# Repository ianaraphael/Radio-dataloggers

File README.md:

# SNICE_therm
Snow/ice thermistor dataloggers

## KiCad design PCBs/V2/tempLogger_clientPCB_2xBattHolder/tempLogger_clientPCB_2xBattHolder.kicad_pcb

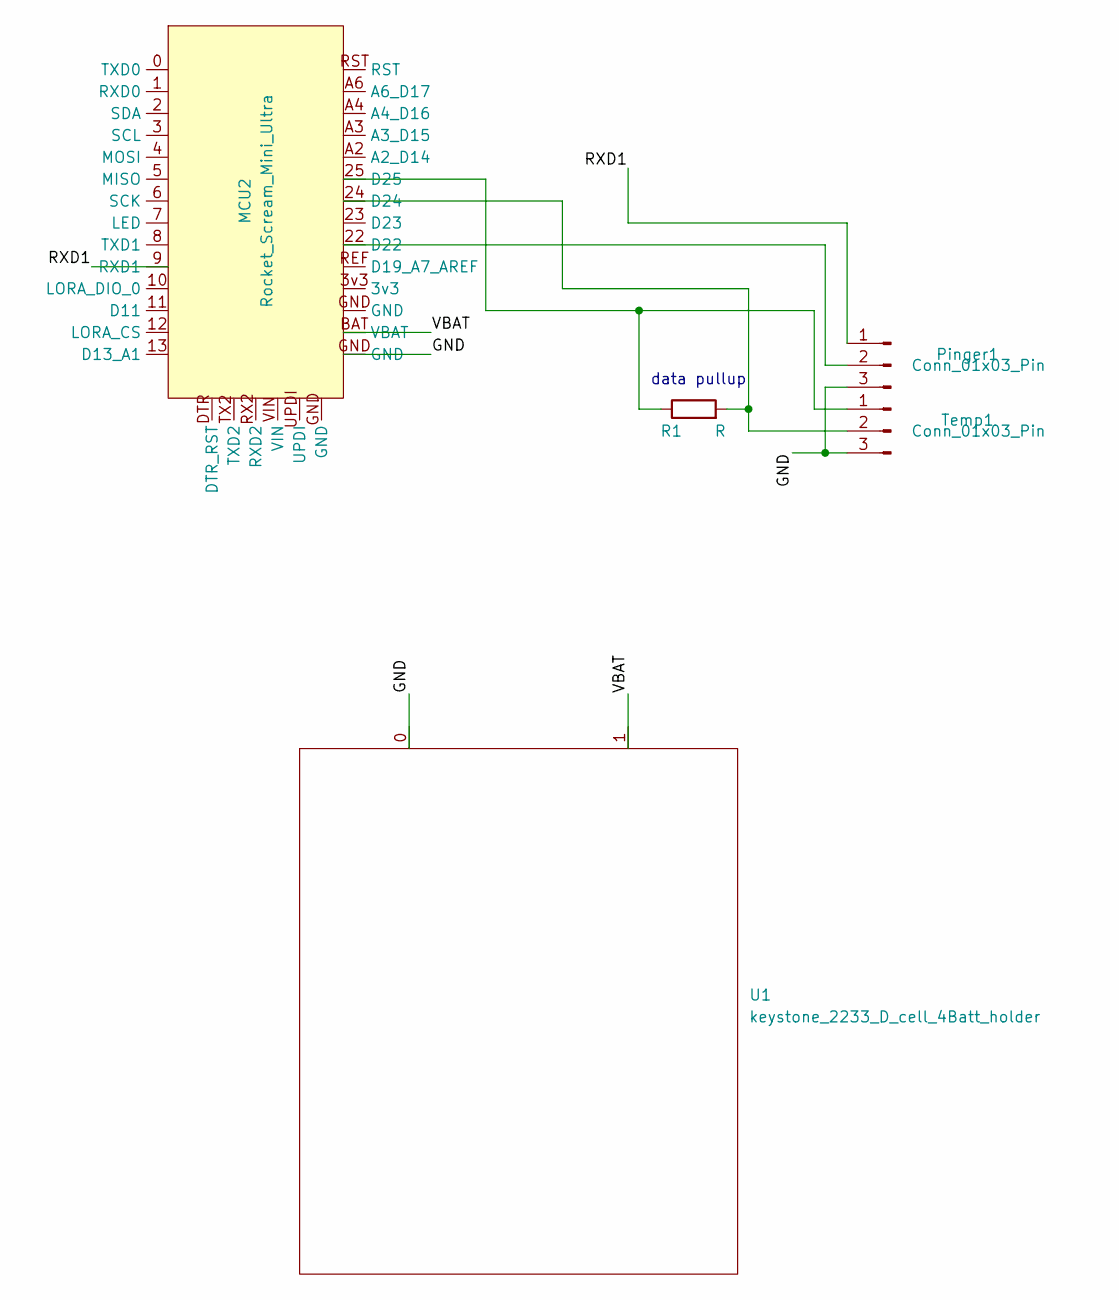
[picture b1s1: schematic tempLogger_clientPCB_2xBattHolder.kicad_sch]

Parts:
MCU2: Rocket_Scream_Mini_Ultra
Pinger1: Conn_01x03_Pin; Molex_KK-254_AE-6410-03A_1x03_P2.54mm_Vertical
R1: R; R_Axial_DIN0204_L3.6mm_D1.6mm_P7.62mm_Horizontal
Temp1: Conn_01x03_Pin; Molex_KK-254_AE-6410-03A_1x03_P2.54mm_Vertical
U1: keystone_2233_D_cell_4Batt_holder; BatteryHolder_Keystone_2233_4Cell

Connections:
/GND: MCU2.GND, Pinger1.3, Temp1.3, U1.0
/RXD1: MCU2.9 (RXD1), Pinger1.1
/VBAT: MCU2.BAT (VBAT), U1.1
unnamed: MCU2.22 (D22), Pinger1.2
unnamed: MCU2.24 (D24), R1.2, Temp1.2
unnamed: MCU2.25 (D25), R1.1, Temp1.1

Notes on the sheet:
data pullup

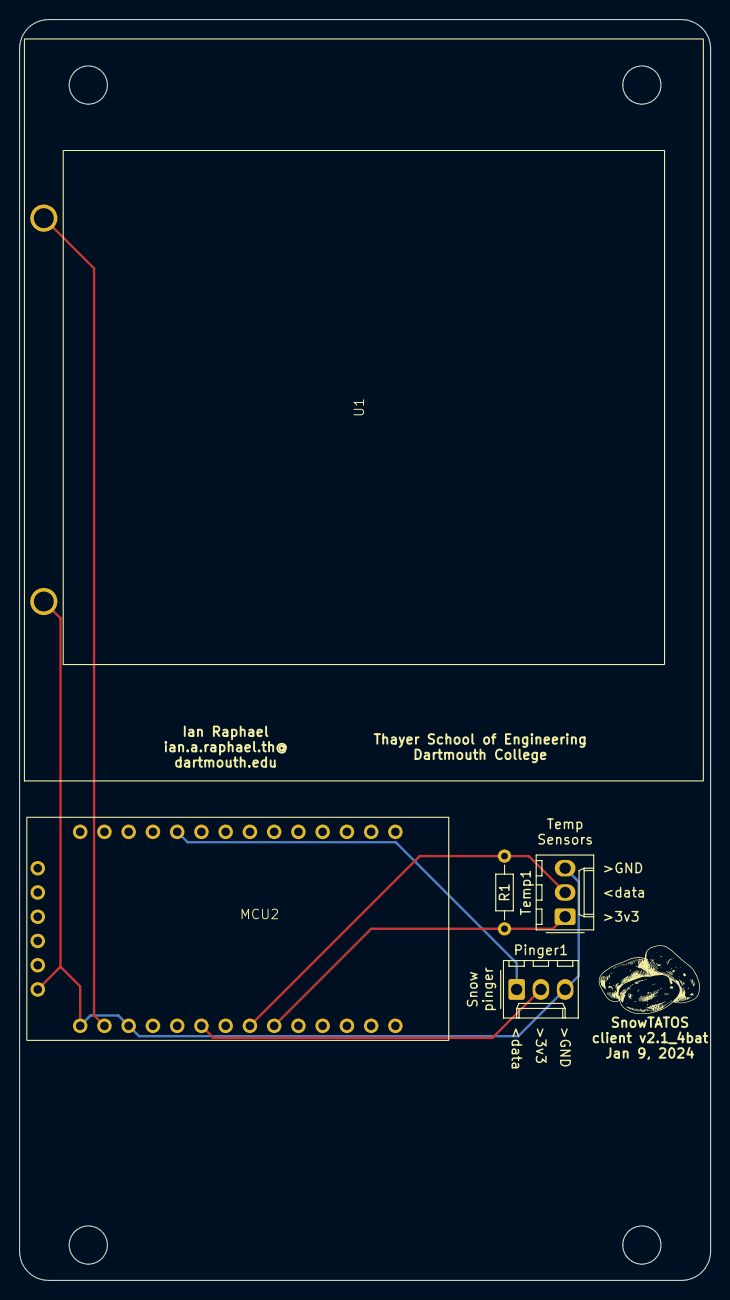
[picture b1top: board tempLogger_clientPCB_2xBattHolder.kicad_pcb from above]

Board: 2 copper layers, 72.4 x 132.1 mm, 5 parts (0 on the bottom side), 6 nets.

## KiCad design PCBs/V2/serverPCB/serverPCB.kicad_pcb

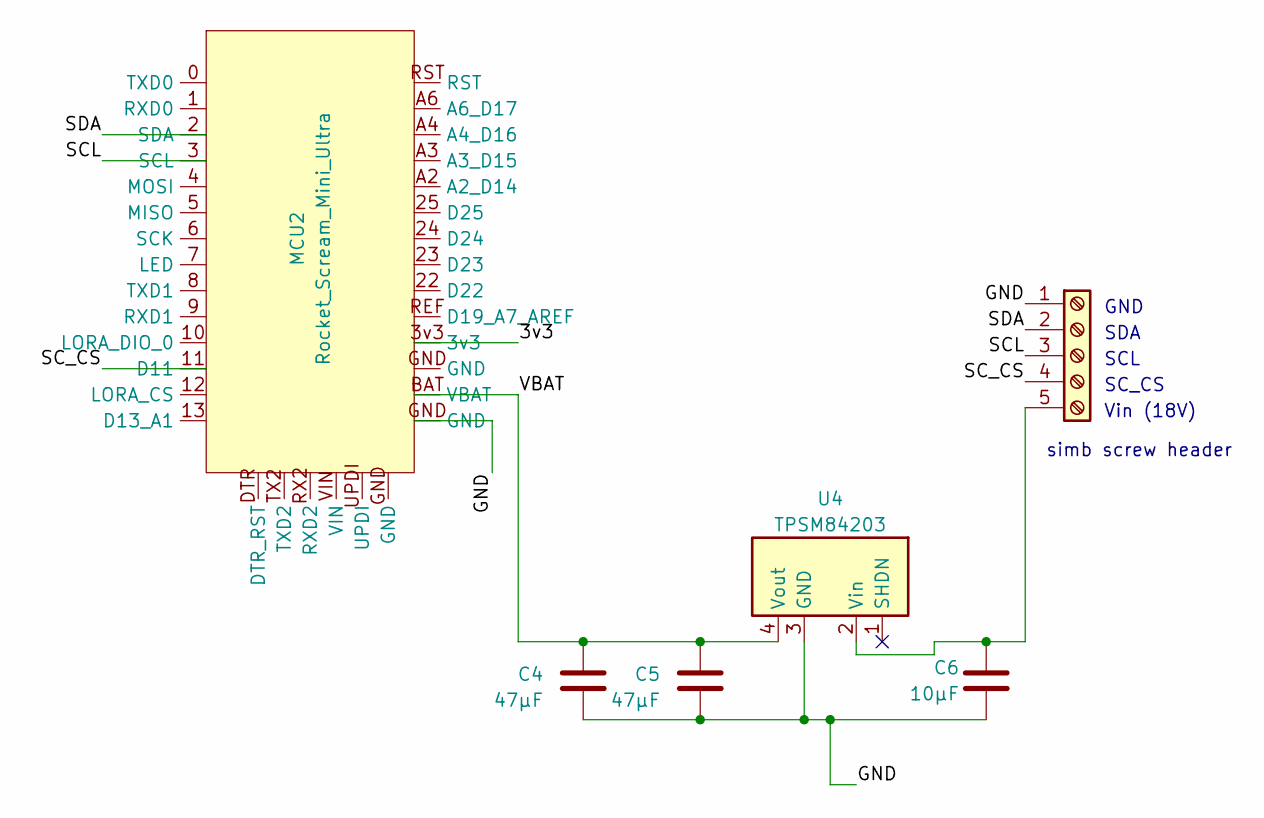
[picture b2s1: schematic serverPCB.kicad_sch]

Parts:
C4, C5: 47µF; CP_Radial_Tantal_D4.5mm_P2.50mm
C6: 10µF; CP_Radial_Tantal_D4.5mm_P2.50mm
J2: Screw_Terminal_01x04; TerminalBlock_Phoenix_MPT-0,5-5-2.54_1x05_P2.54mm_Horizontal
MCU2: Rocket_Scream_Mini_Ultra
U4: TPSM84203; Pololu_D24V5F9

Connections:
/3v3: MCU2.3v3
/GND: C4.2, C5.2, C6.2, J2.1, MCU2.GND, U4.3 (GND)
/SCL: J2.3, MCU2.3 (SCL)
/SC_CS: J2.4, MCU2.11 (D11)
/SDA: J2.2, MCU2.2 (SDA)
/VBAT: C4.1, C5.1, MCU2.BAT (VBAT), U4.4 (Vout)
unnamed: C6.1, J2.5, U4.2 (Vin)

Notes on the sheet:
simb screw header
SCL
SC_CS
SDA
Vin (18V)
GND

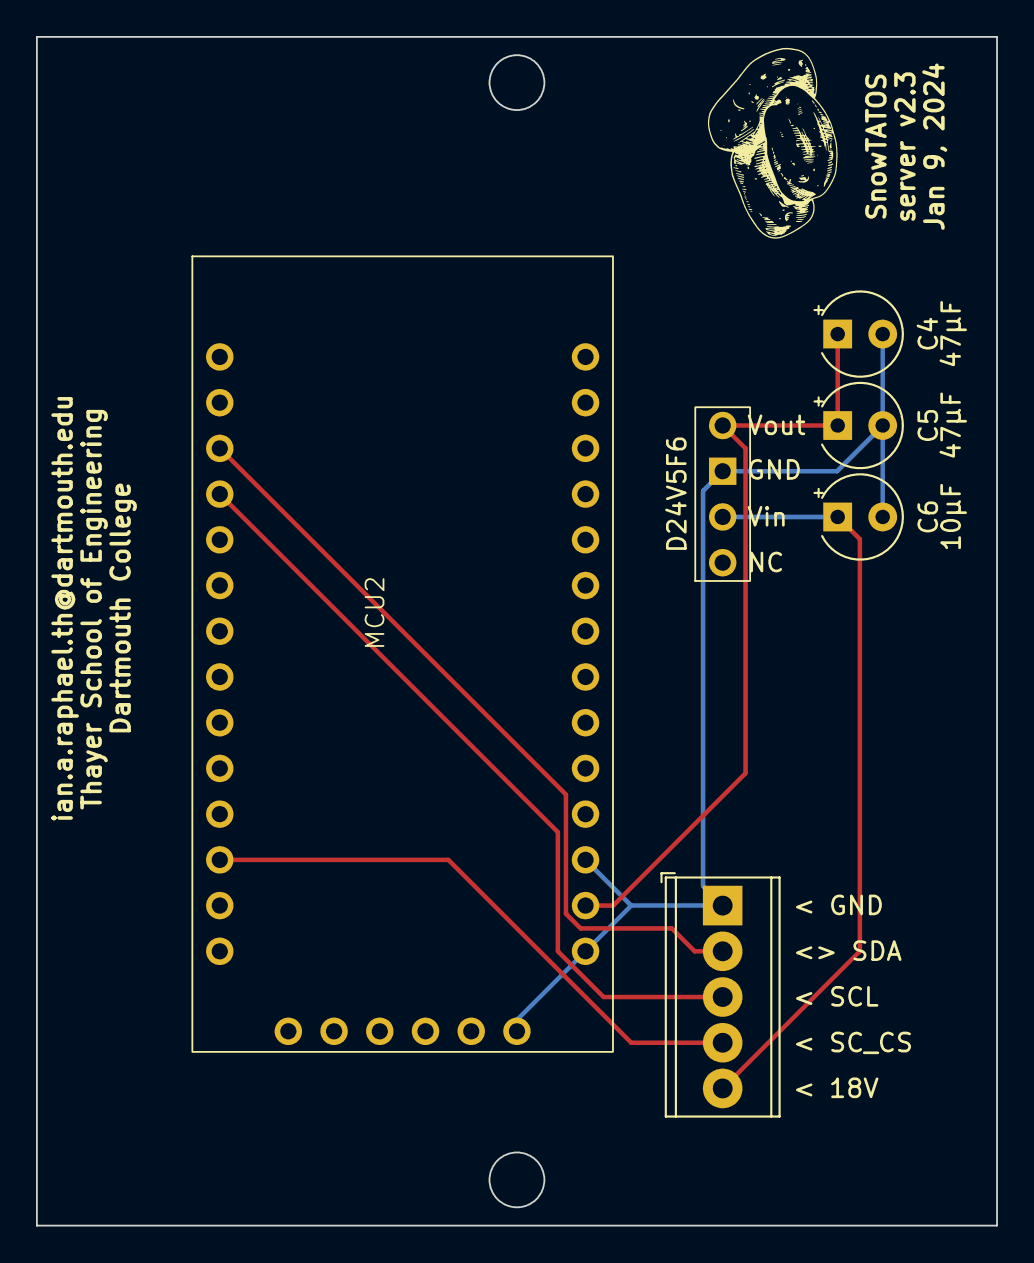
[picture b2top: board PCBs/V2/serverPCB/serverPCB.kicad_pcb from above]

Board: 2 copper layers, 53.3 x 66.0 mm, 6 parts (0 on the bottom side), 6 nets.

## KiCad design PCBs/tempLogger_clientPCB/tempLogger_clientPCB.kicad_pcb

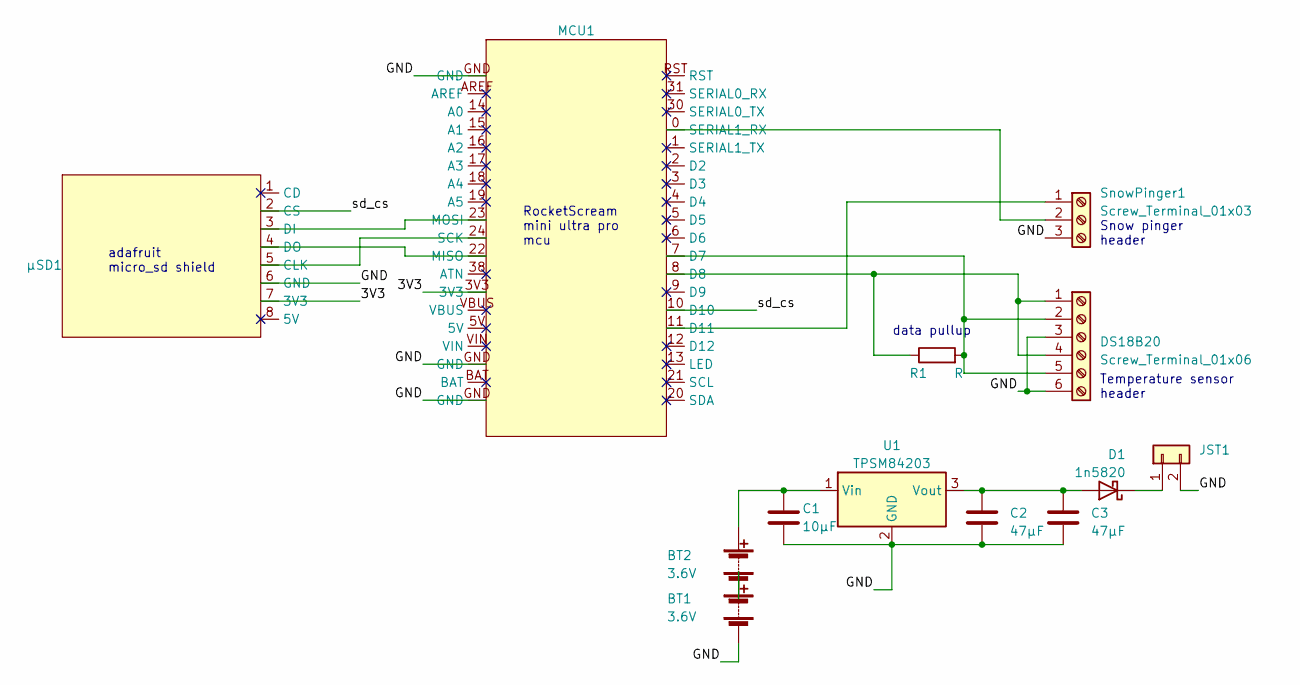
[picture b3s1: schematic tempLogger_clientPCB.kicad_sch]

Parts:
BT1, BT2: 3.6V; battery_c_cell_solderTabs
C1: 10µF; CP_Radial_Tantal_D4.5mm_P2.50mm
C2, C3: 47µF; CP_Radial_Tantal_D4.5mm_P2.50mm
D1: 1n5820; D_DO-41_SOD81_P10.16mm_Horizontal
DS18B20: Screw_Terminal_01x06; TerminalBlock_Phoenix_MPT-0,5-6-2.54_1x06_P2.54mm_Horizontal
JST1: JST male flying leads; TestPoint_2Pads_Pitch5.08mm_Drill1.3mm
MCU1: Rocket_Scream_Mini_Ultra_Pro
R1: R; R_Axial_DIN0204_L3.6mm_D1.6mm_P7.62mm_Horizontal
SnowPinger1: Screw_Terminal_01x03; TerminalBlock_TE_282834-3_1x03_P2.54mm_Horizontal
U1: TPSM84203; Converter_DCDC_TRACO_TSR-1_THT
µSD1: micro_sd_cardReader_adafruit

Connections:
/3V3: MCU1.3V3, µSD1.7 (3V3)
/GND: BT1.2 (-), C1.2, C2.2, C3.2, DS18B20.3, DS18B20.6, JST1.2, MCU1.GND, SnowPinger1.3, U1.2 (GND), µSD1.6 (GND); also elsewhere on the board
/sd_cs: MCU1.10 (D10), µSD1.2 (CS)
unnamed: BT1.1 (+), BT2.2 (-)
unnamed: BT2.1 (+), C1.1, U1.1 (Vin)
unnamed: C2.1, C3.1, D1.2 (A), U1.3 (Vout)
unnamed: D1.1 (K), JST1.1
unnamed: DS18B20.1, DS18B20.4, MCU1.8 (D8), R1.1
unnamed: DS18B20.2, DS18B20.5, MCU1.7 (D7), R1.2
unnamed 9: MCU1.11 (D11), SnowPinger1.1; also elsewhere on the board
unnamed: MCU1.22 (MISO), µSD1.4 (DO)
unnamed: MCU1.23 (MOSI), µSD1.3 (DI)
unnamed: MCU1.24 (SCK), µSD1.5 (CLK)
unnamed 13: MCU1.0 (SERIAL1_RX), SnowPinger1.2; also elsewhere on the board

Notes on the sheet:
RocketScream mini ultra pro mcu
data pullup
adafruit micro_sd shield
Temperature sensor header
Snow pinger header

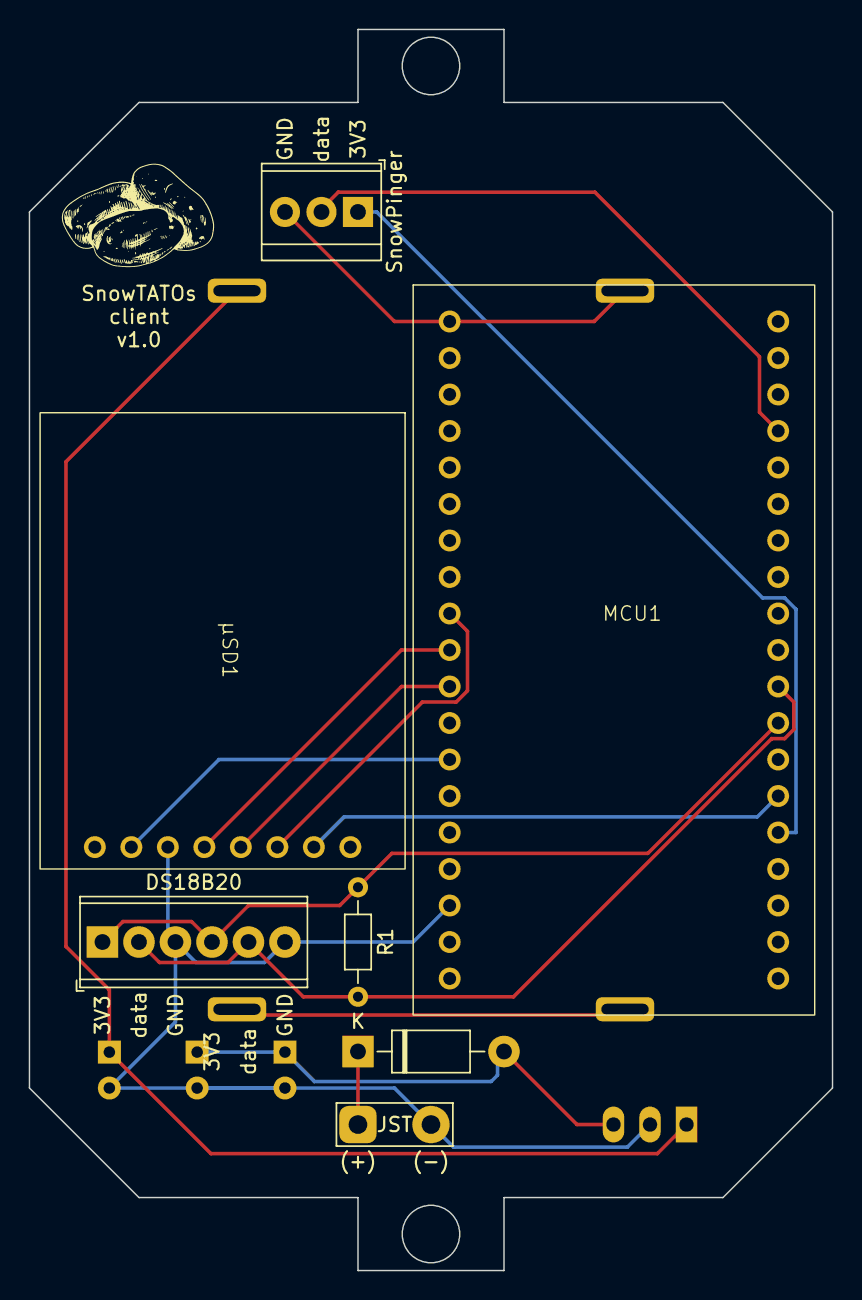
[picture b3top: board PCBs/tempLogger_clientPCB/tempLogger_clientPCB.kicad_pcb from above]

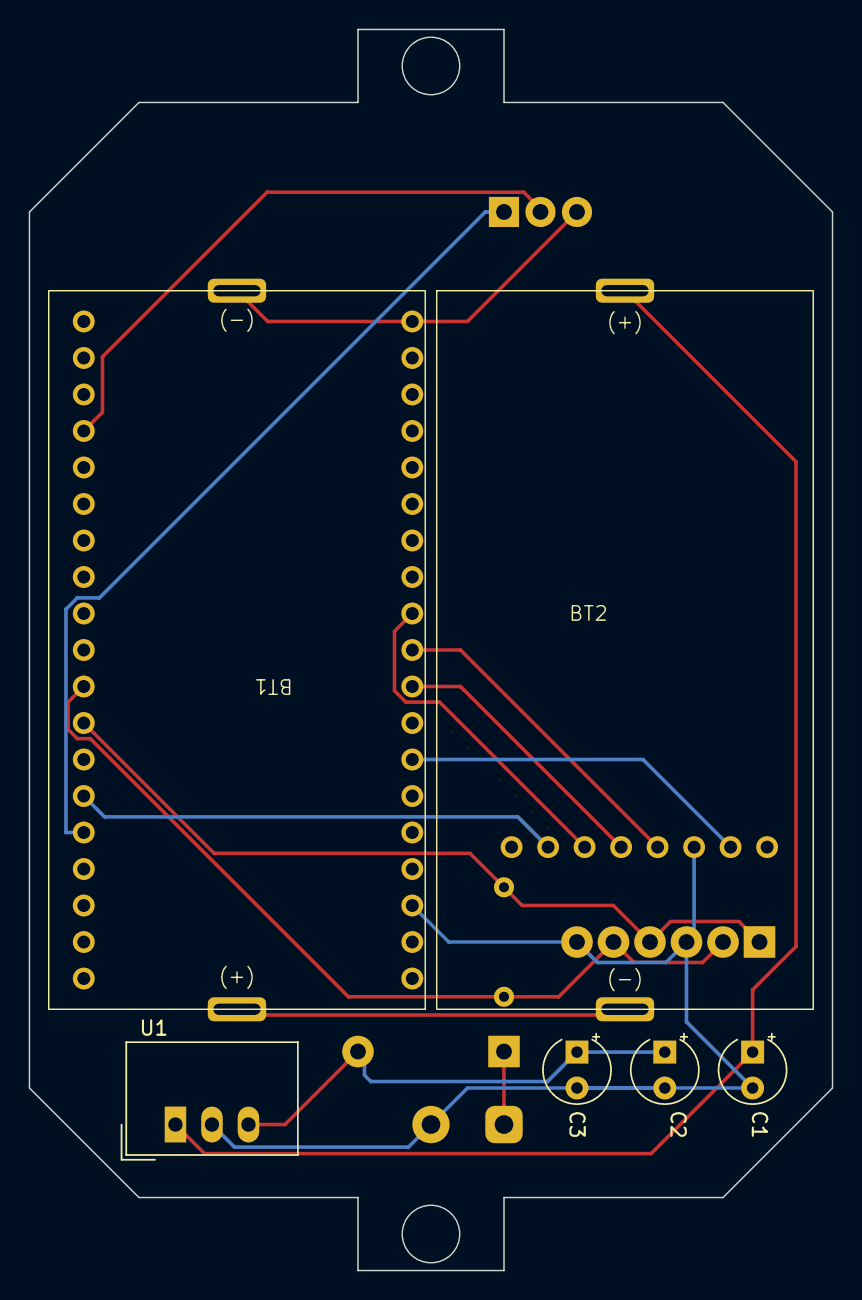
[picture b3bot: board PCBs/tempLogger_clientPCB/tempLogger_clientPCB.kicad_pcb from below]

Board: 2 copper layers, 55.9 x 86.4 mm, 13 parts (6 on the bottom side), 14 nets.

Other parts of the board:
SnowPinger: Screw_Terminal_01x03; TerminalBlock_TE_282834-3_1x03_P2.54mm_Horizontal

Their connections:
/GND: SnowPinger.3; also elsewhere on the board
unnamed 9: SnowPinger.1; also elsewhere on the board
unnamed 13: SnowPinger.2; also elsewhere on the board

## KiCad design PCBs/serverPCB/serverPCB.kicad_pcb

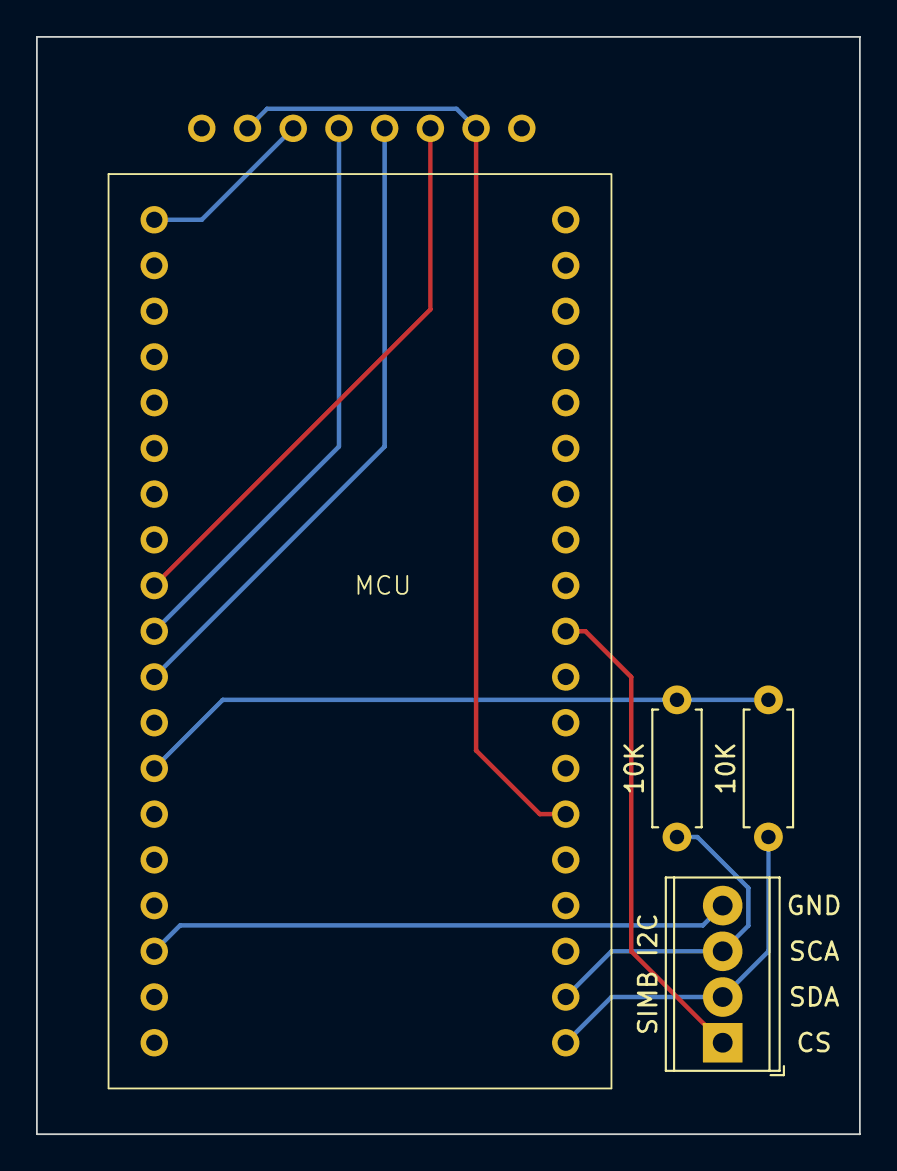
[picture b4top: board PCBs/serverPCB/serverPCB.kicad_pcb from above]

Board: 2 copper layers, 45.7 x 61.0 mm, 5 parts (1 on the bottom side), 9 nets.

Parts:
10K, 10K#2: 10K; R_Axial_DIN0207_L6.3mm_D2.5mm_P7.62mm_Horizontal
MCU: Rocket_Scream_Mini_Ultra_Pro
SIMB I2C: Screw_Terminal_01x04; TerminalBlock_Phoenix_MPT-0,5-4-2.54_1x04_P2.54mm_Horizontal
µSD: micro_sd_cardReader_adafruit

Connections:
/3V3: 10K.2, 10K#2.2, MCU.3V3
/GND: MCU.GND, SIMB I2C.4, µSD.6 (GND)
/sd_cs: MCU.10 (D10), µSD.2 (CS), µSD.7 (3V3)
unnamed: MCU.6 (D6), SIMB I2C.1
unnamed: 10K.1, MCU.20 (SDA), SIMB I2C.2
unnamed: 10K#2.1, MCU.21 (SCL), SIMB I2C.3
unnamed: MCU.22 (MISO), µSD.4 (DO)
unnamed: MCU.23 (MOSI), µSD.3 (DI)
unnamed: MCU.24 (SCK), µSD.5 (CLK)

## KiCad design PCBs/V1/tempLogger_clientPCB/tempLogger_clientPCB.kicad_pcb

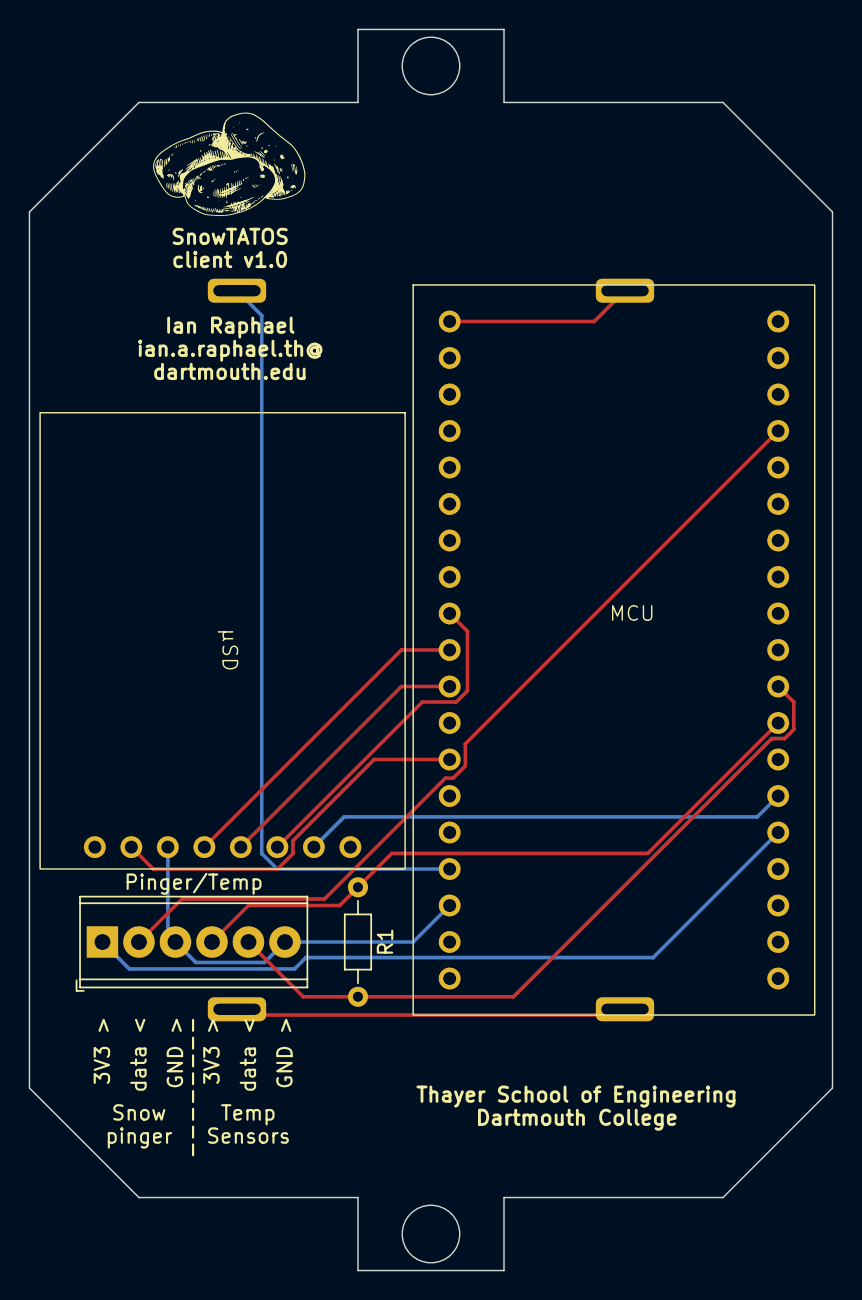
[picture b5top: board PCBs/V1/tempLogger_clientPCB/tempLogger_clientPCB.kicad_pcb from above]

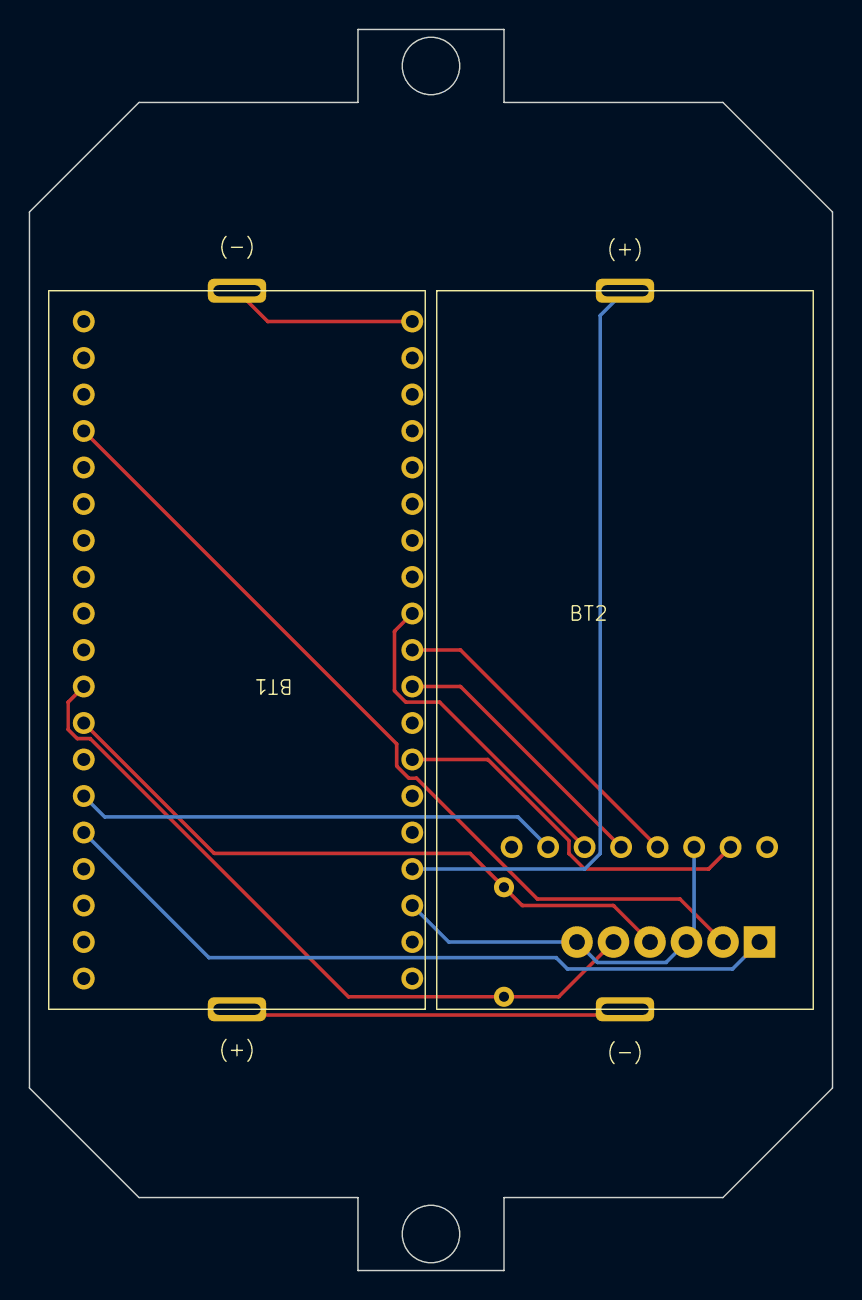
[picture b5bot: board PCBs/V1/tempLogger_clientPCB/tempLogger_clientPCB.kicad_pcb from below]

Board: 2 copper layers, 55.9 x 86.4 mm, 6 parts (2 on the bottom side), 12 nets.

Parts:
BT1, BT2: 3.6V; battery_c_cell_solderTabs
MCU: Rocket_Scream_Mini_Ultra_Pro
Pinger/Temp: Screw_Terminal_01x06; TerminalBlock_Phoenix_MPT-0,5-6-2.54_1x06_P2.54mm_Horizontal
R1: R; R_Axial_DIN0204_L3.6mm_D1.6mm_P7.62mm_Horizontal
µSD: micro_sd_cardReader_adafruit

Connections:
/3V3: MCU.3V3, µSD.7 (3V3)
/GND: BT1.2 (-), MCU.GND, Pinger/Temp.3, Pinger/Temp.6, µSD.6 (GND)
/sd_cs: MCU.10 (D10), µSD.2 (CS)
unnamed: BT1.1 (+), BT2.2 (-)
unnamed: BT2.1 (+), MCU.VIN
unnamed: MCU.7 (D7), Pinger/Temp.5, R1.2
unnamed: MCU.8 (D8), Pinger/Temp.4, R1.1
unnamed: MCU.11 (D11), Pinger/Temp.1
unnamed: MCU.22 (MISO), µSD.4 (DO)
unnamed: MCU.23 (MOSI), µSD.3 (DI)
unnamed: MCU.24 (SCK), µSD.5 (CLK)
unnamed: MCU.0 (SERIAL1_RX), Pinger/Temp.2

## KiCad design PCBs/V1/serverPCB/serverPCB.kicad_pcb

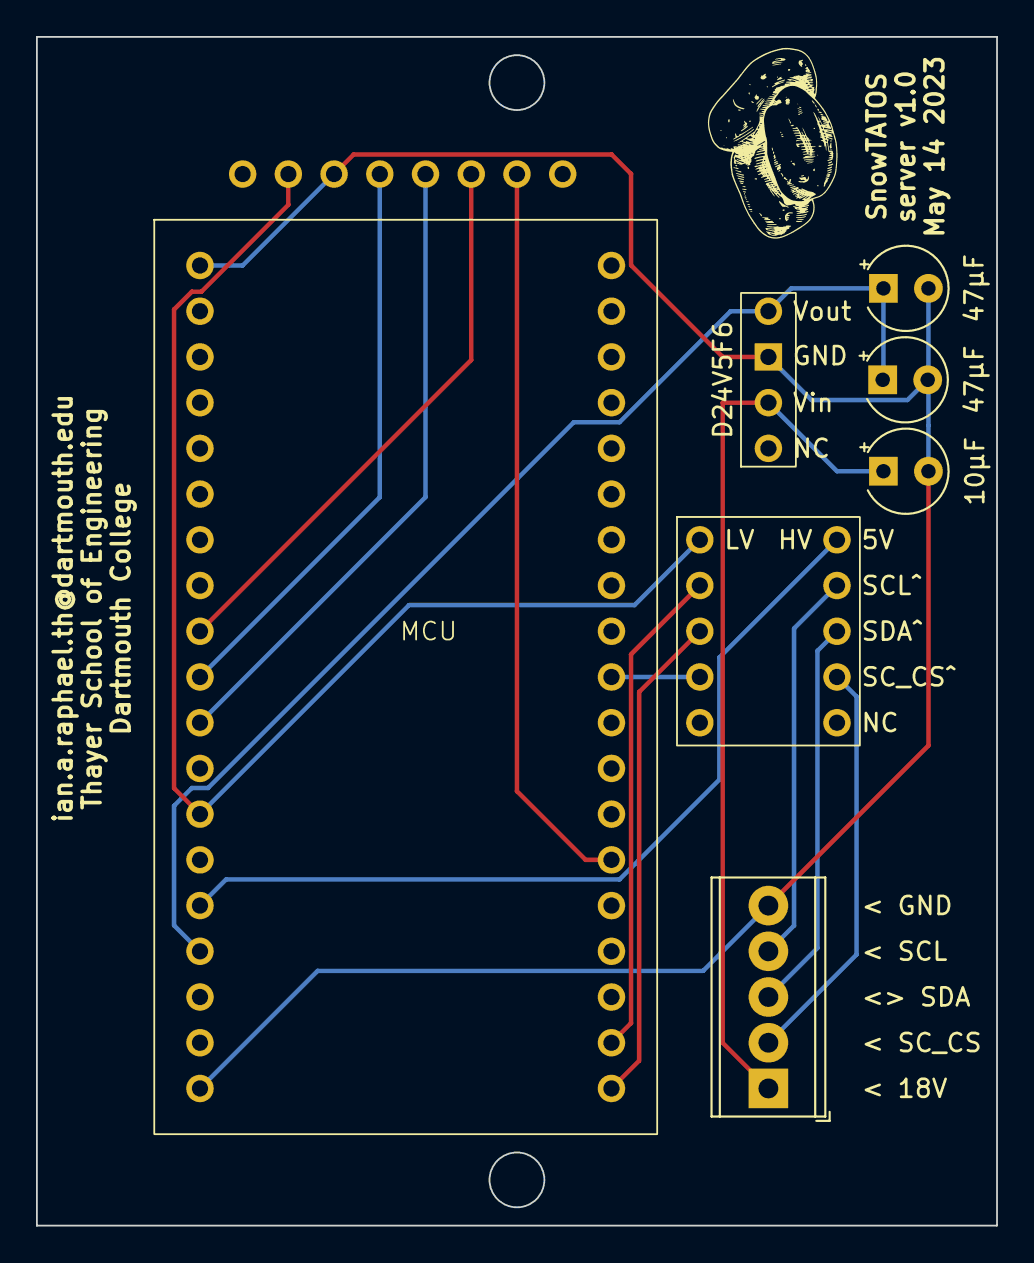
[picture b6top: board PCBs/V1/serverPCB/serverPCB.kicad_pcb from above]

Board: 2 copper layers, 53.3 x 66.0 mm, 8 parts (1 on the bottom side), 15 nets.

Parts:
C1: 10µF; CP_Radial_Tantal_D4.5mm_P2.50mm
C2, C3: 47µF; CP_Radial_Tantal_D4.5mm_P2.50mm
J1: Screw_Terminal_01x04; TerminalBlock_Phoenix_MPT-0,5-5-2.54_1x05_P2.54mm_Horizontal
MCU: Rocket_Scream_Mini_Ultra_Pro
U1: TPSM84203; Pololu_D24V5F9
U2: Pololu_logicLevelShifter
µSD: micro_sd_cardReader_adafruit

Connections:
/3V3: MCU.3V3, U2.1 (LV), µSD.7 (3V3)
/5V: MCU.5V, U2.6 (HV)
/GND: C1.2, C2.2, C3.2, J1.5, MCU.GND, U1.3 (GND), µSD.6 (GND)
/sd_cs: MCU.10 (D10), µSD.2 (CS)
unnamed: C1.1, J1.1, U1.2 (Vin)
unnamed: J1.2, U2.9 (H3)
unnamed: J1.3, U2.8 (H2)
unnamed: J1.4, U2.7 (H1)
unnamed: MCU.6 (D6), U2.4 (L3)
unnamed: MCU.22 (MISO), µSD.4 (DO)
unnamed: MCU.23 (MOSI), µSD.3 (DI)
unnamed: MCU.24 (SCK), µSD.5 (CLK)
unnamed: MCU.21 (SCL), U2.2 (L1)
unnamed: MCU.20 (SDA), U2.3 (L2)
unnamed: C2.1, C3.1, MCU.VIN, U1.4 (Vout)

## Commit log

2021-07-09 initial commit for radio datalogger code. Pulling Pat's code for piezo loggers.
2021-07-12 first readthrough of Pat's code. Some small errors caught.
2021-07-12 Adding pseudo code for the temp loggers + copying over pat's code to provide framework for v1.
2021-07-13 adding MOSAiC legacy code from David's repo
2021-07-19 Addressing/reading multiple therms
2021-07-19 Reading snow pinger digital output and error checking the string.
2021-07-30 temp sensor class for reading and packaging data
2021-07-30 Finished functionality for initing and reading a temp sensors class object
2021-08-02 functional class for initing, reading snow pinger class object
2021-08-13 Simple client and server functionality
2021-09-03 simple client and server plus half finished advanced clien
2021-09-03 Client and server updates towards functionality
2021-09-03 fixing compiler errors
2021-09-03 running with functionality errors
2022-08-09 moving utqiagvik code to individual module directory.
2022-08-09 working simple radio connection between client and server. no data transmission yet.
2022-08-09 sending data string directly after read. No file check yet.
2022-08-09 strange behavior between client and server. unexpected new failure to ack
2022-09-02 buffered file read on client side
2022-09-02 transmitting buffered messages to server with single client safeguard
2022-09-02 starting to save data to file on server side.
2022-09-08 communicating filename & filesize between server and client. untested but compiling.
2022-09-10 message type for data and handshake messages implemented on client side
2022-09-21 multi client networking with busy server delay. needs offset timing.
2022-10-14 random anti-collision delay working.
2022-10-16 fixed rollover on client's interpretation of server file length. deep sleep working.
2022-10-18 added pinger and moved radio transmission etc to functions
2022-10-19 misc changes
2022-11-30 client code as deployed in Utqiagvik, November 2022. Wake timer manually set to 1hr.
2023-02-28 edits working with Daniel.
2023-03-23 PCB dev mostly
2023-03-27 library dev for temp sensors, snow pingers, file handling, radio
2023-03-27 library dev
2023-04-04 i2c dev
2023-04-05 working with interrupts
2023-05-03 mostly pcb updates. beginning of arcwatch deployment code. updates to libs
2023-05-04 integrating i2c comms to server
2023-05-10 i2c comms ready for simb test
2023-05-10 fixing typos
2023-05-10 fixing serial/serial usb calls
2023-05-18 pcb edits
2023-06-15 semi-working packed bitstream. hangs on pinger value packing.
2023-06-16 overhauling to work with byte stream instead of text.
2023-06-19 compiling and functioning, bug with packing/unpacking client temps
2023-06-20 working code!!!
2023-07-27 last ditch changes to integrate into simb
2023-07-30 added iridium comms for server
2023-08-26 need to commit
2023-09-22 deployment version arcwatch 2023
2023-11-28 v2 pcbs
2023-11-28 updated client side rtc and server syncing
2023-12-18 fully updated but untested server/node code for new mini ultra boards
2023-12-20 successful server integration into barebones simb program and full simb suite with dummy buffer
2024-01-03 implemented full mm resolution for pingers, + voltage monitoring
2024-01-09 fixed packetIndex ISR bug in TC code. added state 0.
2024-01-21 fixed pinger read error
2024-01-24 flashed for deployment on ARCSIX 1,2,3,4
2024-01-25 flashed for arcwatch
2024-02-05 deployed ARCSIX
